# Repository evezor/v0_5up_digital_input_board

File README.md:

# 5up Digital Input Board
*please note this board has been deprecated.

An edge board containing five opto isolated inputs.  All inputs are active HIGH. Each input comes with an input pin, a 5v and a gnd connection. 

If I were to do this again, I would probably make a jumper that can switch between the 5v and whatever the bus voltage was. 

source files can be found here: https://github.com/evezor/v0_5up_digital_input_board

This board uses the Evezor Stamp STMF405 MCU

source: https://github.com/evezor/Evezor-Stamp-STMF405

Evezor® and all associated marks, logos, and designs are registered trademarks and protected by copyright. Unauthorized use or reproduction of these trademarks and copyrighted materials is strictly prohibited.

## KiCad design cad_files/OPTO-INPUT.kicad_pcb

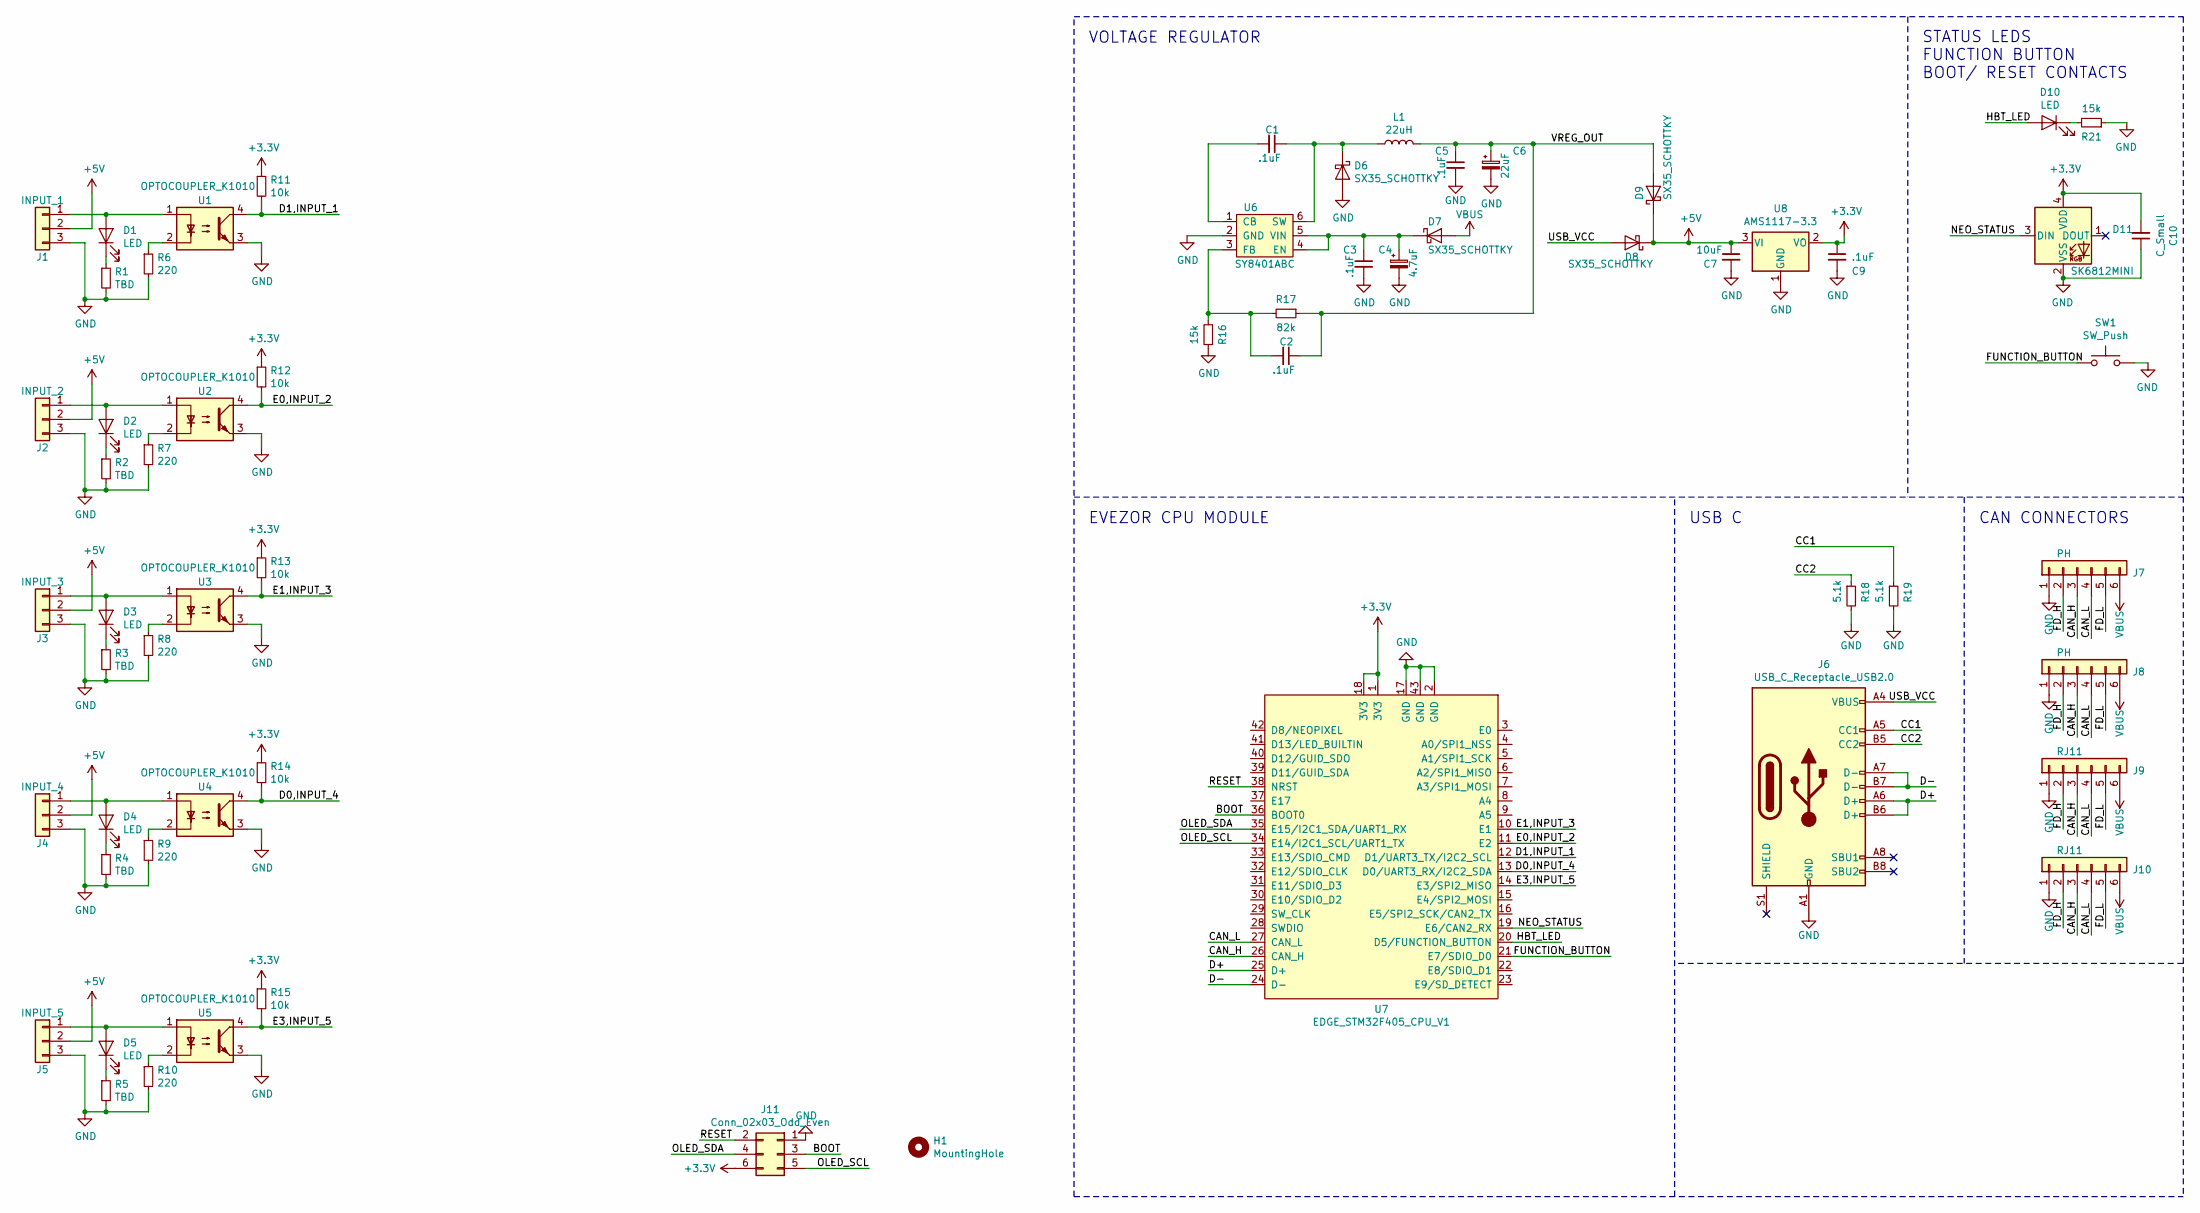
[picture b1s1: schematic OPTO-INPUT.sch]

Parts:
C1, C2, C3, C5, C9: .1uF; C_0603_1608Metric
C4: 4.7uF; C_0805_2012Metric
C6: 22uF; C_0805_2012Metric
C7: 10uF; C_0805_2012Metric
C10: C_Small; C_0603_1608Metric
D1, D2, D3, D4, D5, D10: LED; LED_0603_1608Metric
D6, D7, D8, D9: SX35_SCHOTTKY; D_SMA
D11: SK6812MINI; LED_SK6812MINI_PLCC4_3.5x3.5mm_P1.75mm
H1: MountingHole; OLED_STANDOFF
J1: INPUT_1; PhoenixContact_MC_1,5_3-G-3.81_1x03_P3.81mm_Horizontal
J2: INPUT_2; PhoenixContact_MC_1,5_3-G-3.81_1x03_P3.81mm_Horizontal
J3: INPUT_3; PhoenixContact_MC_1,5_3-G-3.81_1x03_P3.81mm_Horizontal
J4: INPUT_4; PhoenixContact_MCV_1,5_3-G-3.81_1x03_P3.81mm_Vertical
J5: INPUT_5; PhoenixContact_MCV_1,5_3-G-3.81_1x03_P3.81mm_Vertical
J6: USB_C_Receptacle_USB2.0; USB_C_Receptacle_HRO_TYPE-C-31-M-12
J7, J8: PH; JST_PH_B6B-PH-K_1x06_P2.00mm_Vertical
J9, J10: RJ11; RJ11_C189747_Horizontal
J11: Conn_02x03_Odd_Even; OLED_HEADER
L1: 22uH; INDUCTOR_7.5X6.6_GCDA0630-220MC
R1, R2, R3, R4, R5: TBD; R_0603_1608Metric
R6, R7, R8, R9, R10: 220; R_0603_1608Metric
R11, R12, R13, R14, R15: 10k; R_0603_1608Metric
R16, R21: 15k; R_0603_1608Metric
R17: 82k; R_0603_1608Metric
R18, R19: 5.1k; R_0603_1608Metric
SW1: SW_Push; SWITCH_2x3_SMD_TACTILE_GREEN
U1, U2, U3, U4, U5: OPTOCOUPLER_K1010; OPTOCOUPLER_K10104CTLD
U6: SY8401ABC; SOT-23-6
U7: EDGE_STM32F405_CPU_V1; EDGE_STAMP
U8: AMS1117-3.3; SOT-223-3_TabPin2

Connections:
+3V3: C9.1, C10.2, D11.4 (VDD), J11.6, R11.1, R12.1, R13.1, R14.1, R15.1, U7.1 (3V3), U7.18 (3V3), U8.2 (VO); also elsewhere on the board
+5V: C7.1, D8.1 (K), D9.1 (K), J1.2, J2.2, J3.2, J4.2, J5.2, U8.3 (VI)
/BOOT: J11.3, U7.36 (BOOT0)
/CAN_H: J7.3, J8.3, J9.3, J10.3, U7.26 (CAN_H)
/CAN_L: J7.4, J8.4, J9.4, J10.4, U7.27 (CAN_L)
/CC1: J6.A5 (CC1), R19.1
/CC2: J6.B5 (CC2), R18.1
/D0,INPUT_4: R14.2, U4.4, U7.13 (D0/UART3_RX/I2C2_SDA)
/D1,INPUT_1: R11.2, U1.4, U7.12 (D1/UART3_TX/I2C2_SCL)
/D+: J6.A6 (D+), J6.B6 (D+), U7.25 (D+)
/D-: J6.A7 (D-), J6.B7 (D-), U7.24 (D-)
/E0,INPUT_2: R12.2, U2.4, U7.11 (E2)
/E1,INPUT_3: R13.2, U3.4, U7.10 (E1)
/E3,INPUT_5: R15.2, U5.4, U7.14 (E3/SPI2_MISO)
/FD_H: J7.2, J8.2, J9.2, J10.2
/FD_L: J7.5, J8.5, J9.5, J10.5
/FUNCTION_BUTTON: SW1.1, U7.21 (E7/SDIO_D0)
/HBT_LED: D10.2 (A), U7.20 (D5/FUNCTION_BUTTON)
/NEO_STATUS: D11.3 (DIN), U7.19 (E6/CAN2_RX)
/OLED_SCL: J11.5, U7.34 (E14/I2C1_SCL/UART1_TX)
/OLED_SDA: J11.4, U7.35 (E15/I2C1_SDA/UART1_RX)
/RESET: J11.2, U7.38 (NRST)
/USB_VCC: D8.2 (A), J6.A4 (VBUS), J6.A9 (VBUS), J6.B4 (VBUS), J6.B9 (VBUS)
/VREG_OUT: C2.1, C5.1, C6.1, D9.2 (A), L1.2, R17.1
GND: C3.2, C4.2, C5.2, C6.2, C7.2, C9.2, C10.1, D6.2 (A), D11.2 (VSS), J1.3, J2.3, J3.3, J4.3, J5.3, J6.A1 (GND), J6.A12 (GND), J6.B1 (GND), J6.B12 (GND), J7.1, J8.1, J9.1, J10.1, J11.1, R1.2, R2.2, R3.2, R4.2, R5.2, R6.2, R7.2, R8.2, R9.2, R10.2, R16.1, R18.2, R19.2, R21.1, SW1.2, U1.3, U2.3, U3.3, U4.3, U5.3, U6.2 (GND), U7.2 (GND), U7.17 (GND), U7.43 (GND), U8.1 (GND)
unnamed: C1.1, D6.1 (K), L1.1, U6.6 (SW)
unnamed: C1.2, U6.1 (CB)
unnamed: C2.2, R16.2, R17.2, U6.3 (FB)
unnamed: C3.1, C4.1, D7.1 (K), U6.4 (EN), U6.5 (VIN)
unnamed: D1.1 (K), R1.1
unnamed: D1.2 (A), J1.1, U1.1
unnamed: D2.1 (K), R2.1
unnamed: D2.2 (A), J2.1, U2.1
unnamed: D3.1 (K), R3.1
unnamed: D3.2 (A), J3.1, U3.1
unnamed: D4.1 (K), R4.1
unnamed: D4.2 (A), J4.1, U4.1
unnamed: D5.1 (K), R5.1
unnamed: D5.2 (A), J5.1, U5.1
unnamed: D10.1 (K), R21.2
unnamed: R6.1, U1.2
unnamed: R7.1, U2.2
unnamed: R8.1, U3.2
unnamed: R9.1, U4.2
unnamed: R10.1, U5.2
VBUS: D7.2 (A), J7.6, J8.6, J9.6, J10.6

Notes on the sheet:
EVEZOR CPU MODULE
USB C
CAN CONNECTORS
STATUS LEDS FUNCTION BUTTON BOOT/ RESET CONTACTS
VOLTAGE REGULATOR

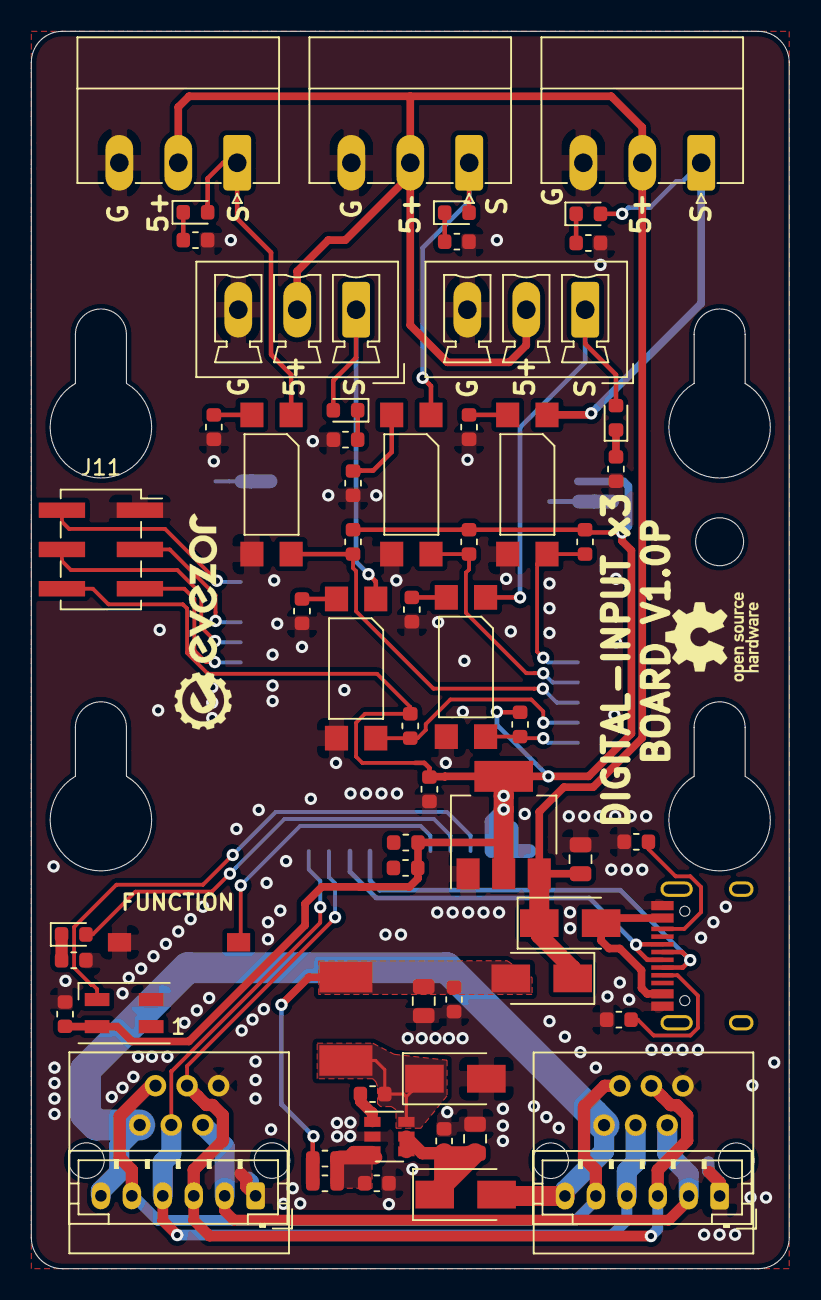
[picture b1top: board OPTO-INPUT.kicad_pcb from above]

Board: 2 copper layers, 49.0 x 80.0 mm, 64 parts (1 on the bottom side), 46 nets.

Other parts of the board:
R20, R22: R_Small; R_0603_1608Metric

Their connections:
+3V3: R20.2, R22.2; also elsewhere on the board

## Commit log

2020-11-06 readme
2020-11-06 first
2020-11-06 add datasheet
2020-11-15 add simple can message recieved script
2023-09-11 add pics
